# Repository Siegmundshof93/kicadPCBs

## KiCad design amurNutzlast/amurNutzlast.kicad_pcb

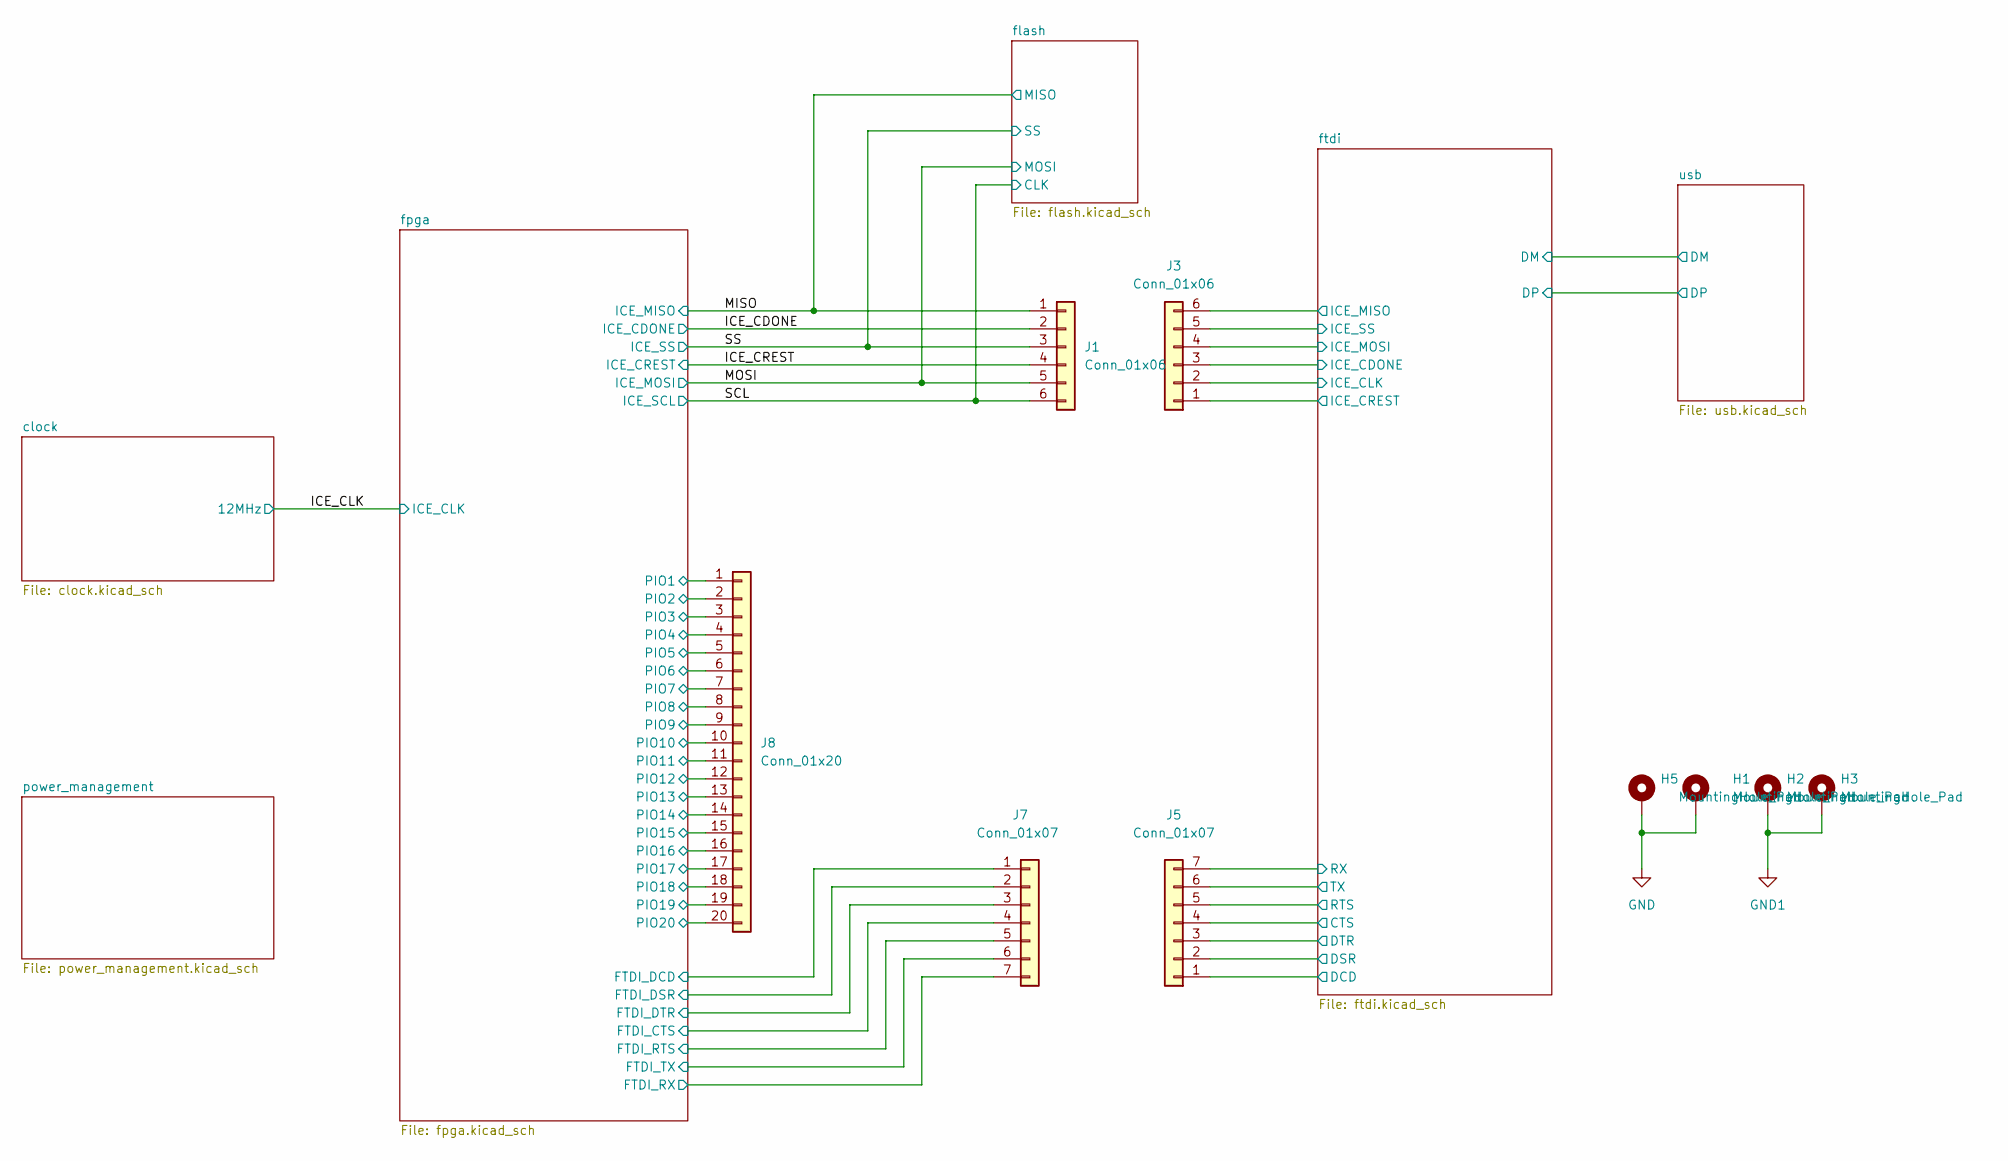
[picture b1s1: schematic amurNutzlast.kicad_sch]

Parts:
H1, H2, H3, H5: MountingHole_Pad; MountingHole_2.5mm_Pad_Via
J1, J3: Conn_01x06; PinHeader_2x03_P2.54mm_Vertical
J5, J7: Conn_01x07; PinHeader_1x07_P2.54mm_Vertical
J8: Conn_01x20; PinHeader_2x10_P2.54mm_Vertical

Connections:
/ICE_CDONE: J1.2; also elsewhere on the board
/ICE_CREST: J1.4; also elsewhere on the board
/MISO: J1.1; also elsewhere on the board
/MOSI: J1.5; also elsewhere on the board
/SCL: J1.6; also elsewhere on the board
/SS: J1.3; also elsewhere on the board
/fpga/FTDI_CTS: J7.4; also elsewhere on the board
/fpga/FTDI_DCD: J7.1; also elsewhere on the board
/fpga/FTDI_DSR: J7.2; also elsewhere on the board
/fpga/FTDI_DTR: J7.3; also elsewhere on the board
/fpga/FTDI_RTS: J7.5; also elsewhere on the board
/fpga/FTDI_RX: J7.7; also elsewhere on the board
/fpga/FTDI_TX: J7.6; also elsewhere on the board
/fpga/PIO1: J8.1; also elsewhere on the board
/fpga/PIO2: J8.2; also elsewhere on the board
/fpga/PIO3: J8.3; also elsewhere on the board
/fpga/PIO4: J8.4; also elsewhere on the board
/fpga/PIO5: J8.5; also elsewhere on the board
/fpga/PIO6: J8.6; also elsewhere on the board
/fpga/PIO7: J8.7; also elsewhere on the board
/fpga/PIO8: J8.8; also elsewhere on the board
/fpga/PIO9: J8.9; also elsewhere on the board
/fpga/PIO10: J8.10; also elsewhere on the board
/fpga/PIO11: J8.11; also elsewhere on the board
/fpga/PIO12: J8.12; also elsewhere on the board
/fpga/PIO13: J8.13; also elsewhere on the board
/fpga/PIO14: J8.14; also elsewhere on the board
/fpga/PIO15: J8.15; also elsewhere on the board
/fpga/PIO16: J8.16; also elsewhere on the board
/fpga/PIO17: J8.17; also elsewhere on the board
/fpga/PIO18: J8.18; also elsewhere on the board
/fpga/PIO19: J8.19; also elsewhere on the board
/fpga/PIO20: J8.20; also elsewhere on the board
/ftdi/CTS: J5.4; also elsewhere on the board
/ftdi/DCD: J5.1; also elsewhere on the board
/ftdi/DSR: J5.2; also elsewhere on the board
/ftdi/DTR: J5.3; also elsewhere on the board
/ftdi/ICE_CDONE: J3.3; also elsewhere on the board
/ftdi/ICE_CLK: J3.2; also elsewhere on the board
/ftdi/ICE_CREST: J3.1; also elsewhere on the board
/ftdi/ICE_MISO: J3.6; also elsewhere on the board
/ftdi/ICE_MOSI: J3.4; also elsewhere on the board
/ftdi/ICE_SS: J3.5; also elsewhere on the board
/ftdi/RTS: J5.5; also elsewhere on the board
/ftdi/RX: J5.7; also elsewhere on the board
/ftdi/TX: J5.6; also elsewhere on the board

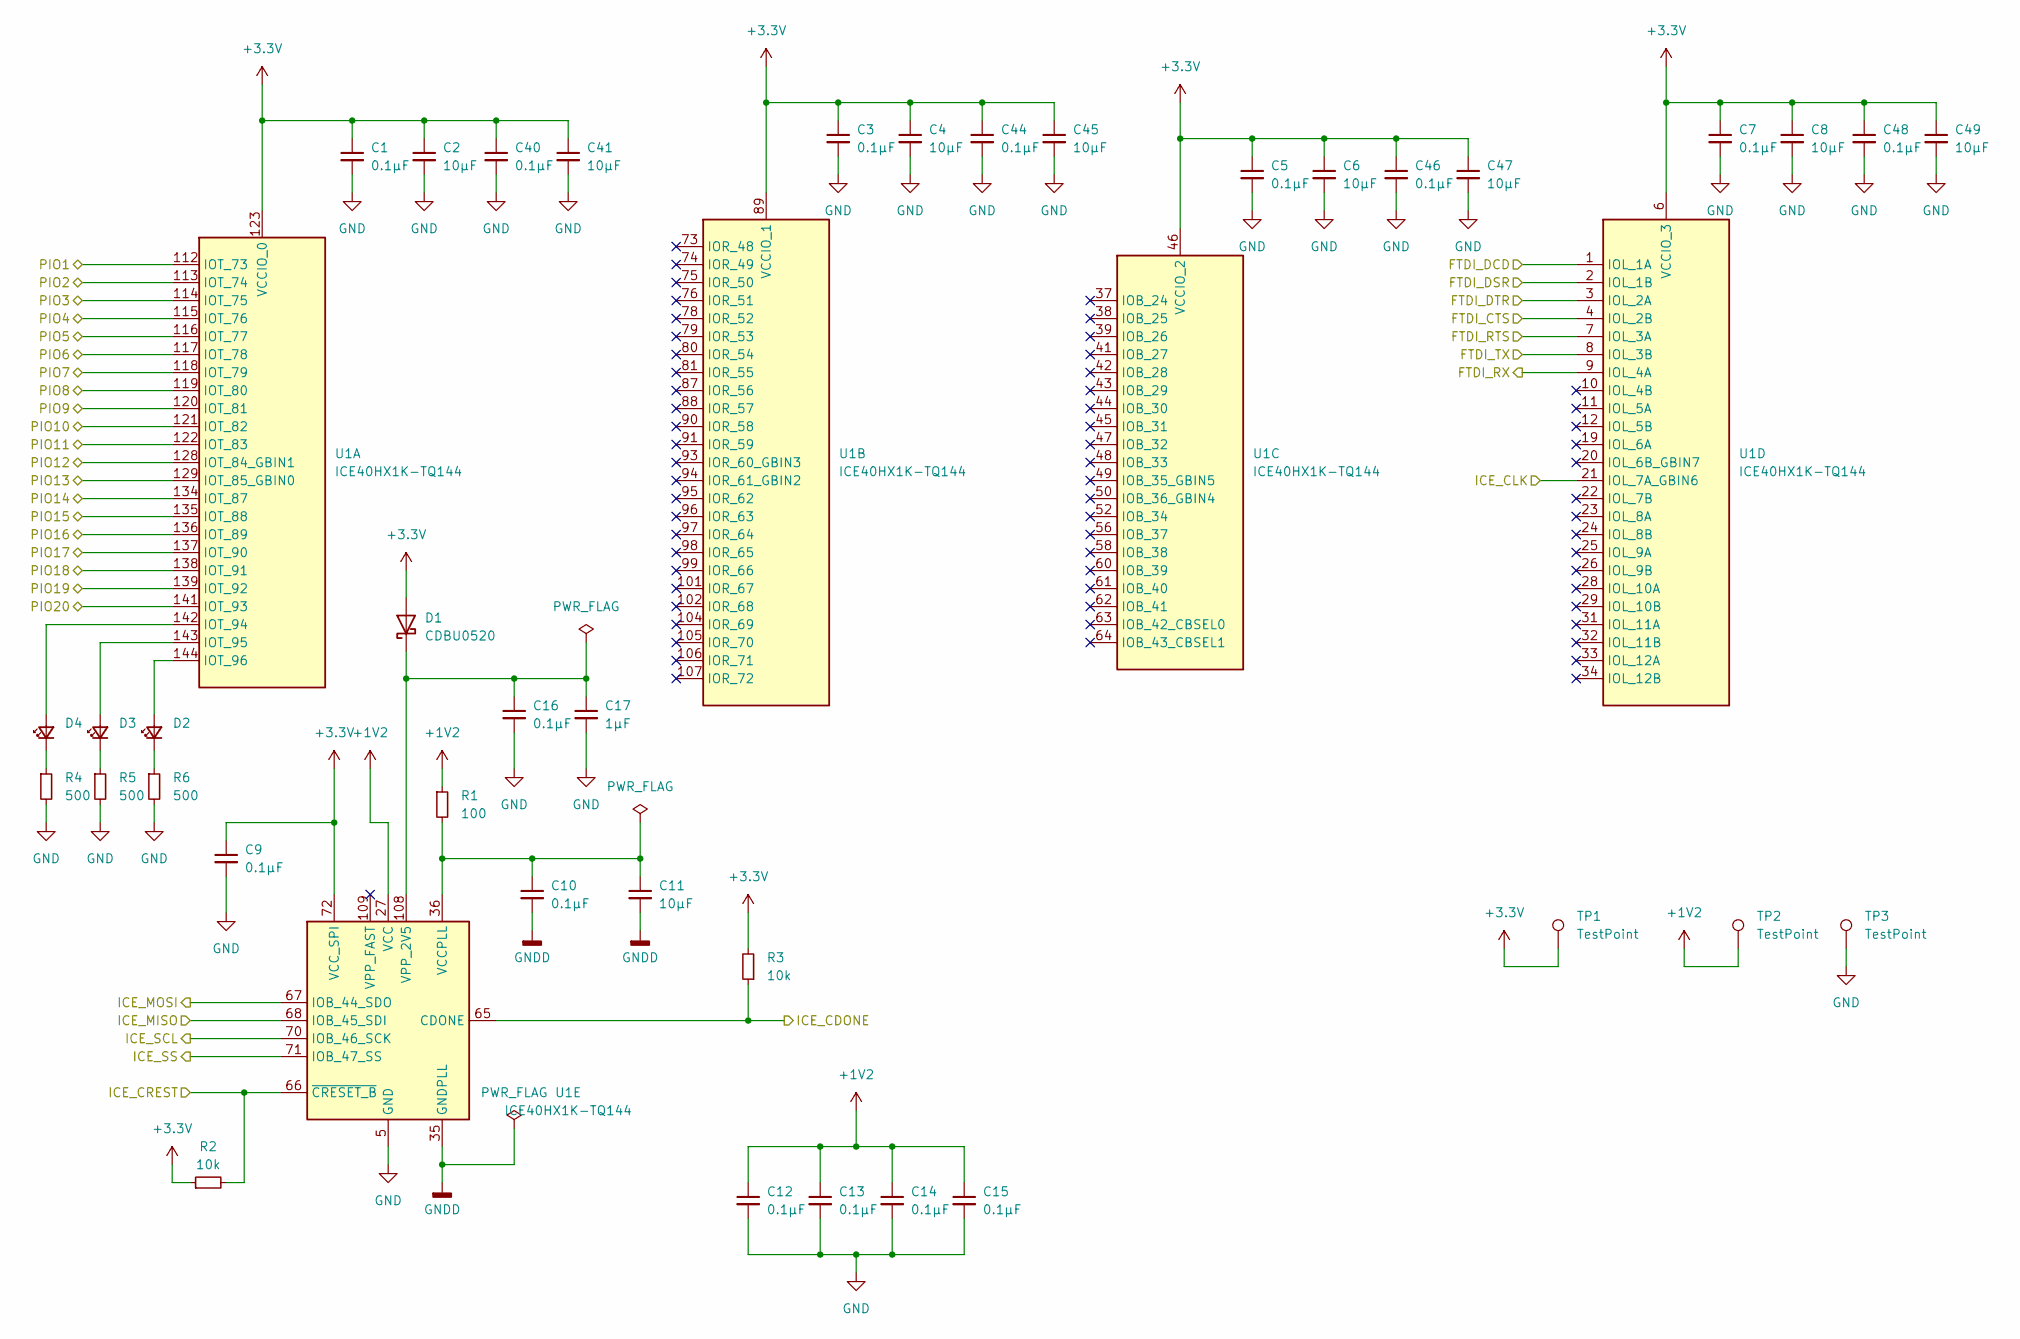
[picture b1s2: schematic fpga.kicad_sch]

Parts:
C1, C3, C5, C7, C9, C10, C12, C13, C14, C15, C16, C40, C44, C46, C48: 0.1µF; C_0603_1608Metric
C2, C4, C6, C8, C11, C41, C45, C47, C49: 10µF; C_0603_1608Metric
C17: 1µF; C_0603_1608Metric
D1: CDBU0520; D_0603_1608Metric
D2, D3, D4: LED_Small; LED_0603_1608Metric
R1: 100; R_0603_1608Metric
R2, R3: 10k; R_0603_1608Metric
R4, R5, R6: 500; R_0603_1608Metric
TP1, TP2, TP3: TestPoint; TestPoint_Pad_D2.5mm
U1: ICE40HX1K-TQ144; TQFP-144_20x20mm_P0.5mm

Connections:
+1V2: C12.1, C13.1, C14.1, C15.1, R1.1, TP2.1, U1.27 (VCC), U1.51 (VCC), U1.92 (VCC), U1.111 (VCC); also elsewhere on the board
/ICE_CDONE: R3.1, U1.65 (CDONE); also elsewhere on the board
/ICE_CLK: U1.21 (IOL_7A_GBIN6); also elsewhere on the board
/ICE_CREST: R2.2, U1.66 (~CRESET_B); also elsewhere on the board
/MISO: U1.68 (IOB_45_SDI); also elsewhere on the board
/MOSI: U1.67 (IOB_44_SDO); also elsewhere on the board
/SCL: U1.70 (IOB_46_SCK); also elsewhere on the board
/SS: U1.71 (IOB_47_SS); also elsewhere on the board
/fpga/FTDI_CTS: U1.4 (IOL_2B); also elsewhere on the board
/fpga/FTDI_DCD: U1.1 (IOL_1A); also elsewhere on the board
/fpga/FTDI_DSR: U1.2 (IOL_1B); also elsewhere on the board
/fpga/FTDI_DTR: U1.3 (IOL_2A); also elsewhere on the board
/fpga/FTDI_RTS: U1.7 (IOL_3A); also elsewhere on the board
/fpga/FTDI_RX: U1.9 (IOL_4A); also elsewhere on the board
/fpga/FTDI_TX: U1.8 (IOL_3B); also elsewhere on the board
/fpga/PIO1: U1.112 (IOT_73); also elsewhere on the board
/fpga/PIO2: U1.113 (IOT_74); also elsewhere on the board
/fpga/PIO3: U1.114 (IOT_75); also elsewhere on the board
/fpga/PIO4: U1.115 (IOT_76); also elsewhere on the board
/fpga/PIO5: U1.116 (IOT_77); also elsewhere on the board
/fpga/PIO6: U1.117 (IOT_78); also elsewhere on the board
/fpga/PIO7: U1.118 (IOT_79); also elsewhere on the board
/fpga/PIO8: U1.119 (IOT_80); also elsewhere on the board
/fpga/PIO9: U1.120 (IOT_81); also elsewhere on the board
/fpga/PIO10: U1.121 (IOT_82); also elsewhere on the board
/fpga/PIO11: U1.122 (IOT_83); also elsewhere on the board
/fpga/PIO12: U1.128 (IOT_84_GBIN1); also elsewhere on the board
/fpga/PIO13: U1.129 (IOT_85_GBIN0); also elsewhere on the board
/fpga/PIO14: U1.134 (IOT_87); also elsewhere on the board
/fpga/PIO15: U1.135 (IOT_88); also elsewhere on the board
/fpga/PIO16: U1.136 (IOT_89); also elsewhere on the board
/fpga/PIO17: U1.137 (IOT_90); also elsewhere on the board
/fpga/PIO18: U1.138 (IOT_91); also elsewhere on the board
/fpga/PIO19: U1.139 (IOT_92); also elsewhere on the board
/fpga/PIO20: U1.141 (IOT_93); also elsewhere on the board
GNDD: C10.2, C11.2, U1.35 (GNDPLL)
unnamed: C16.1, C17.1, D1.1 (K), U1.108 (VPP_2V5)
unnamed: D2.2 (A), U1.144 (IOT_96)
unnamed: D2.1 (K), R6.1
unnamed: D3.2 (A), U1.143 (IOT_95)
unnamed: D3.1 (K), R5.1
unnamed: D4.2 (A), U1.142 (IOT_94)
unnamed: D4.1 (K), R4.1
unnamed: C10.1, C11.1, R1.2, U1.36 (VCCPLL)

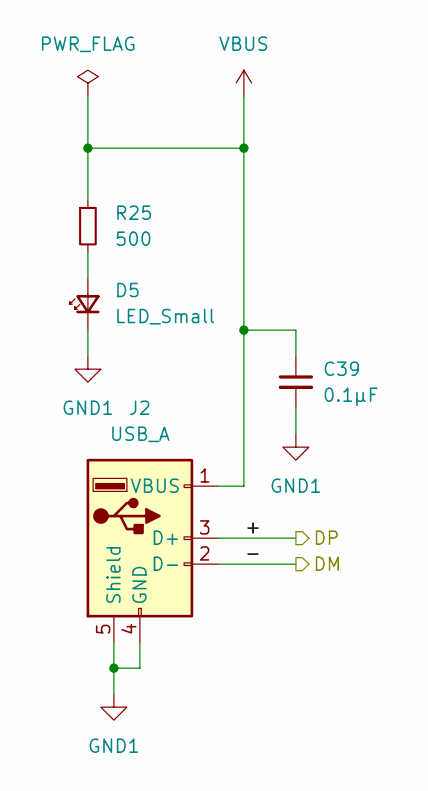
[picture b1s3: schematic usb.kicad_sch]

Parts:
C39: 0.1µF; C_0603_1608Metric
D5: LED_Small; LED_0603_1608Metric
J2: USB_A; USB_A_CNCTech_1001-011-01101_Horizontal
R25: 500; R_0603_1608Metric

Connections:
+5V: J2.2; also elsewhere on the board

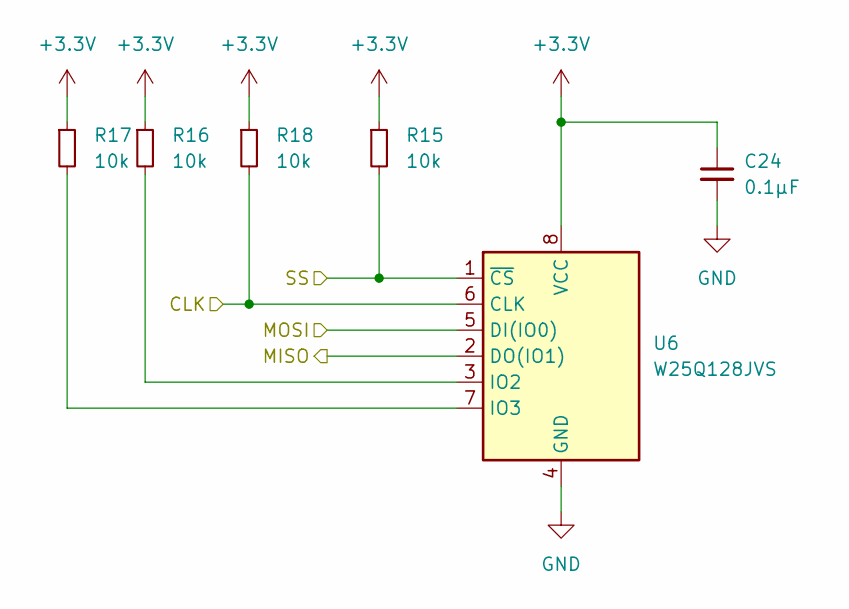
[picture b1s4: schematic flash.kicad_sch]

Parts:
C24: 0.1µF; C_0603_1608Metric
R15, R16, R17, R18: 10k; R_0603_1608Metric
U6: W25Q128JVS; SOIC-8_5.23x5.23mm_P1.27mm

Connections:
/MISO: U6.2 (DO(IO1)); also elsewhere on the board
/MOSI: U6.5 (DI(IO0)); also elsewhere on the board
/SCL: R18.2, U6.6 (CLK); also elsewhere on the board
/SS: R15.2, U6.1 (~CS); also elsewhere on the board
unnamed: R16.2, U6.3 (IO2)
unnamed: R17.2, U6.7 (IO3)

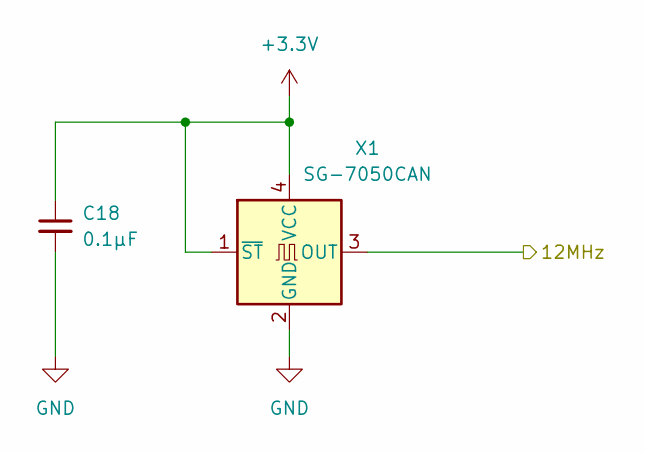
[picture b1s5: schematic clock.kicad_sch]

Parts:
C18: 0.1µF; C_0603_1608Metric
X1: SG-7050CAN; Oscillator_SMD_SeikoEpson_SG8002CA-4Pin_7.0x5.0mm

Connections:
/ICE_CLK: X1.3 (OUT); also elsewhere on the board

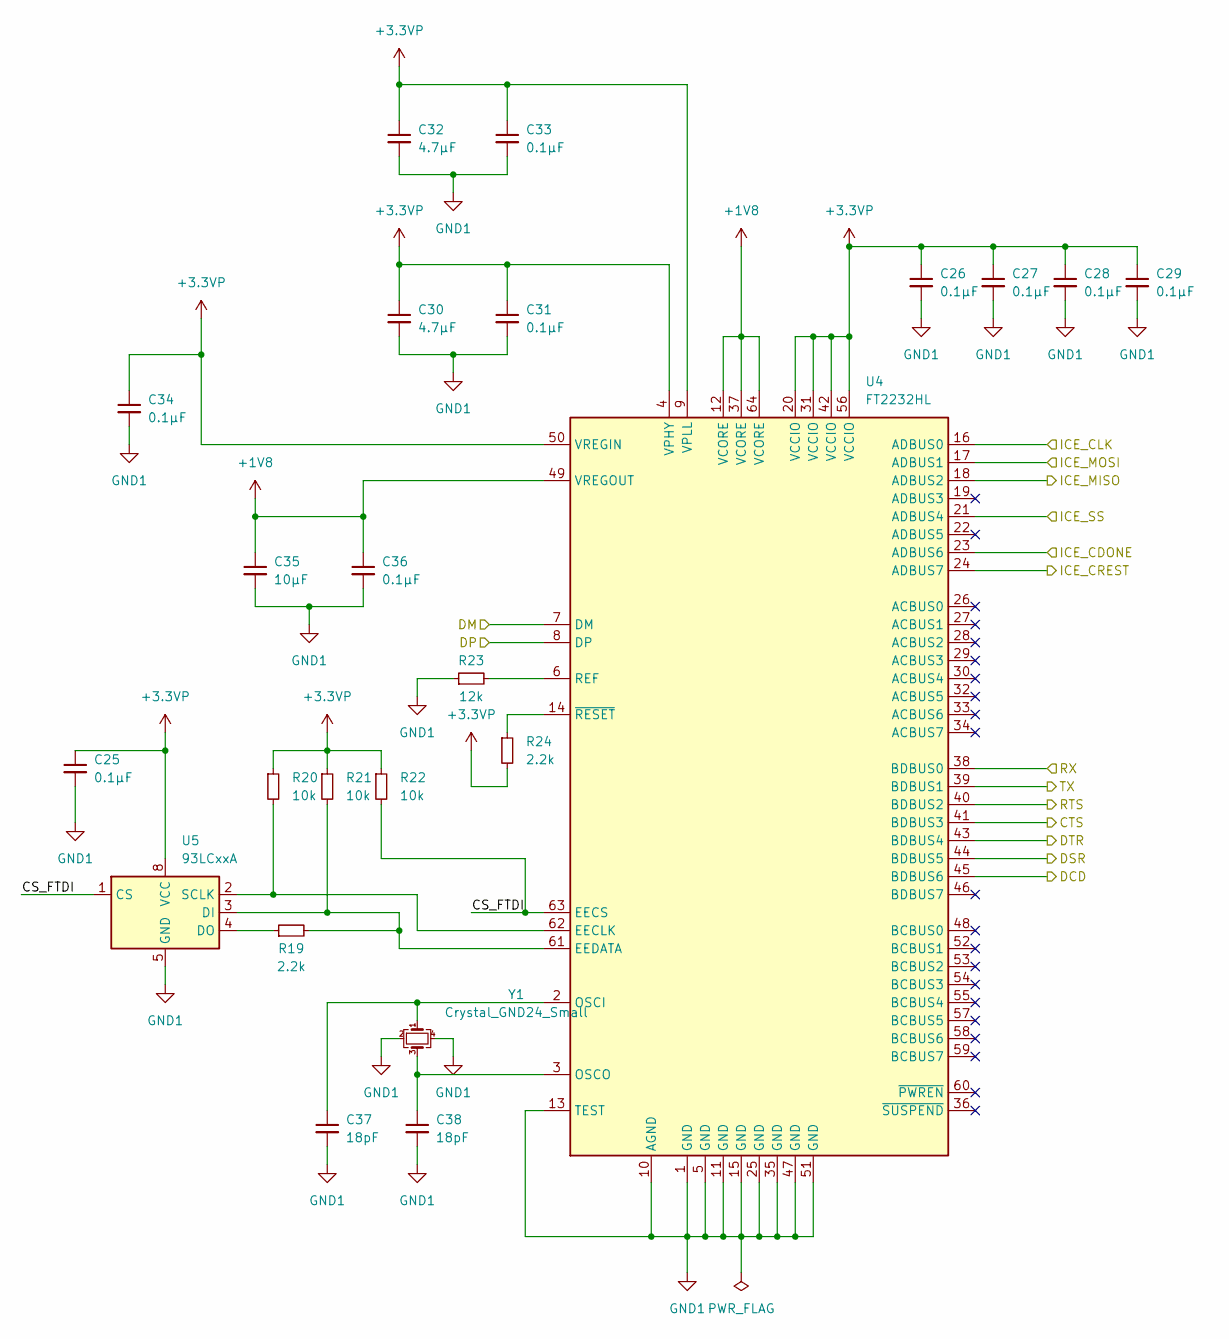
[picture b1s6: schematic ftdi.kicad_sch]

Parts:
C25, C26, C27, C28, C29, C31, C33, C34, C36: 0.1µF; C_0603_1608Metric
C30, C32: 4.7µF; C_0603_1608Metric
C35: 10µF; C_0603_1608Metric
C37, C38: 18pF; C_0603_1608Metric
R19, R24: 2.2k; R_0603_1608Metric
R20, R21, R22: 10k; R_0603_1608Metric
R23: 12k; R_0603_1608Metric
U4: FT2232HL; LQFP-64_10x10mm_P0.5mm
U5: 93LCxxA; SOIC-8_3.9x4.9mm_P1.27mm
Y1: Crystal_GND24_Small; Crystal_SMD_3225-4Pin_3.2x2.5mm

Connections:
+1V8: C35.1, C36.1, U4.12 (VCORE), U4.37 (VCORE), U4.49 (VREGOUT), U4.64 (VCORE)
/ftdi/CS_FTDI: R22.2, U4.63 (EECS), U5.1 (CS)
/ftdi/CTS: U4.41 (BDBUS3); also elsewhere on the board
/ftdi/DCD: U4.45 (BDBUS6); also elsewhere on the board
/ftdi/DSR: U4.44 (BDBUS5); also elsewhere on the board
/ftdi/DTR: U4.43 (BDBUS4); also elsewhere on the board
/ftdi/ICE_CDONE: U4.23 (ADBUS6); also elsewhere on the board
/ftdi/ICE_CLK: U4.16 (ADBUS0); also elsewhere on the board
/ftdi/ICE_CREST: U4.24 (ADBUS7); also elsewhere on the board
/ftdi/ICE_MISO: U4.18 (ADBUS2); also elsewhere on the board
/ftdi/ICE_MOSI: U4.17 (ADBUS1); also elsewhere on the board
/ftdi/ICE_SS: U4.21 (ADBUS4); also elsewhere on the board
/ftdi/RTS: U4.40 (BDBUS2); also elsewhere on the board
/ftdi/RX: U4.38 (BDBUS0); also elsewhere on the board
/ftdi/TX: U4.39 (BDBUS1); also elsewhere on the board
/usb/+: U4.8 (DP); also elsewhere on the board
/usb/-: U4.7 (DM); also elsewhere on the board
unnamed: R20.2, U4.62 (EECLK), U5.2 (SCLK)
unnamed: R19.2, R21.2, U4.61 (EEDATA), U5.3 (DI)
unnamed: C37.1, U4.2 (OSCI), Y1.1
unnamed: C38.1, U4.3 (OSCO), Y1.3
unnamed: R23.2, U4.6 (REF)
unnamed: R24.1, U4.14 (~RESET)
unnamed: R19.1, U5.4 (DO)

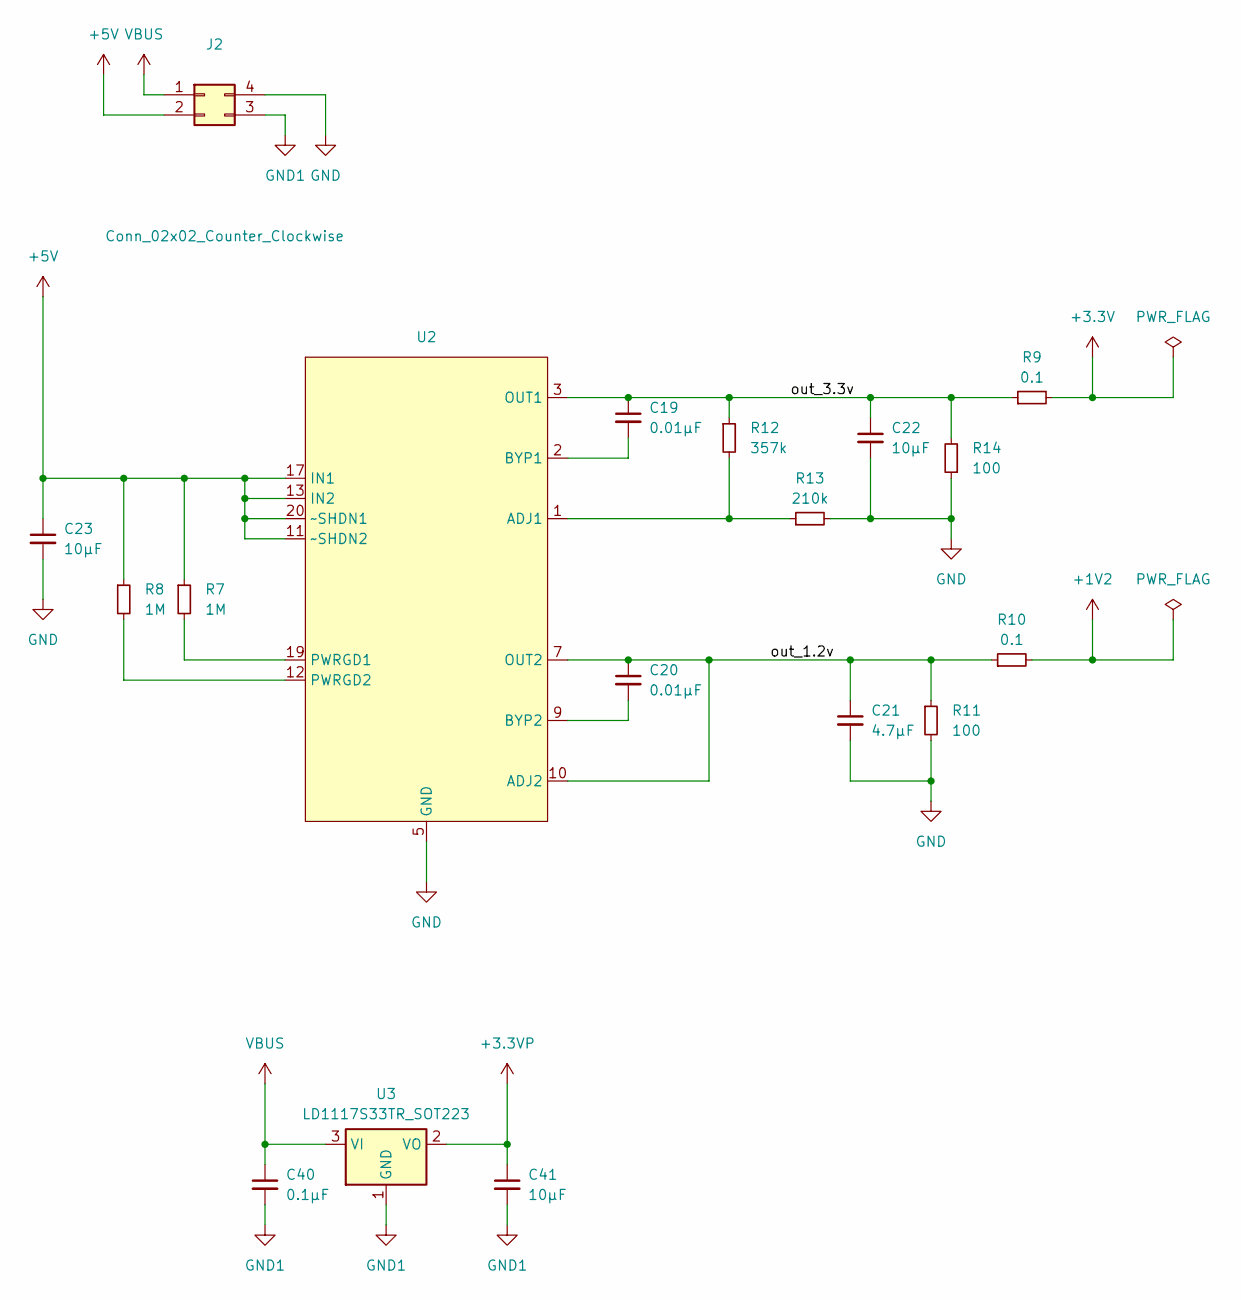
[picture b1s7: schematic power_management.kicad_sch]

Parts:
C19, C20: 0.01µF; C_0603_1608Metric
C21: 4.7µF; C_0603_1608Metric
C22, C23, C41: 10µF; C_0603_1608Metric
C40: 0.1µF; C_0603_1608Metric
J2: Conn_02x02_Counter_Clockwise; PinHeader_2x02_P2.54mm_Vertical
R7, R8: 1M; R_0603_1608Metric
R9, R10: 0.1; R_0603_1608Metric
R11, R14: 100; R_0603_1608Metric
R12: 357k; R_0603_1608Metric
R13: 210k; R_0603_1608Metric
U2: HTSSOP-20-1EP_4.4x6.5mm_P0.65mm_EP2.74x3.86mm
U3: LD1117S33TR_SOT223; SOT-223-3_TabPin2

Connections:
+1V2: R10.2; also elsewhere on the board
+5V: C23.1, J2.2, R7.1, R8.1, U2.11 (~SHDN2), U2.13 (IN2), U2.14 (IN2), U2.17 (IN1), U2.18 (IN1), U2.20 (~SHDN1)
/power_management/out_1.2v: C20.1, C21.1, R10.1, R11.1, U2.7 (OUT2), U2.8 (OUT2), U2.10 (ADJ2)
/power_management/out_3.3v: C19.1, C22.1, R9.1, R12.1, R14.2, U2.3 (OUT1), U2.4 (OUT1)
unnamed: R12.2, R13.1, U2.1 (ADJ1)
unnamed: C19.2, U2.2 (BYP1)
unnamed: C20.2, U2.9 (BYP2)
unnamed: R7.2, U2.19 (PWRGD1)
unnamed: R8.2, U2.12 (PWRGD2)

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
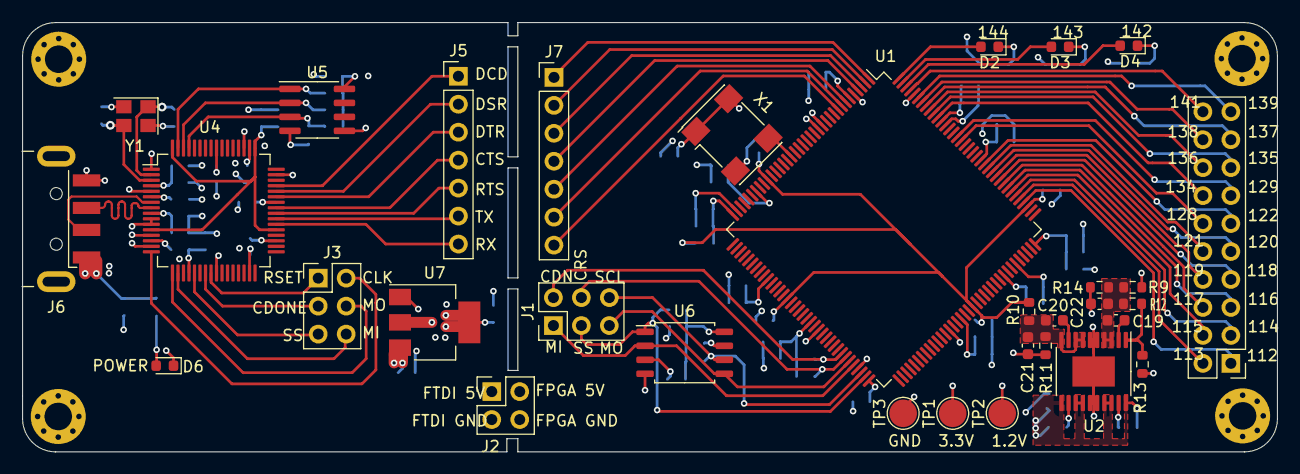
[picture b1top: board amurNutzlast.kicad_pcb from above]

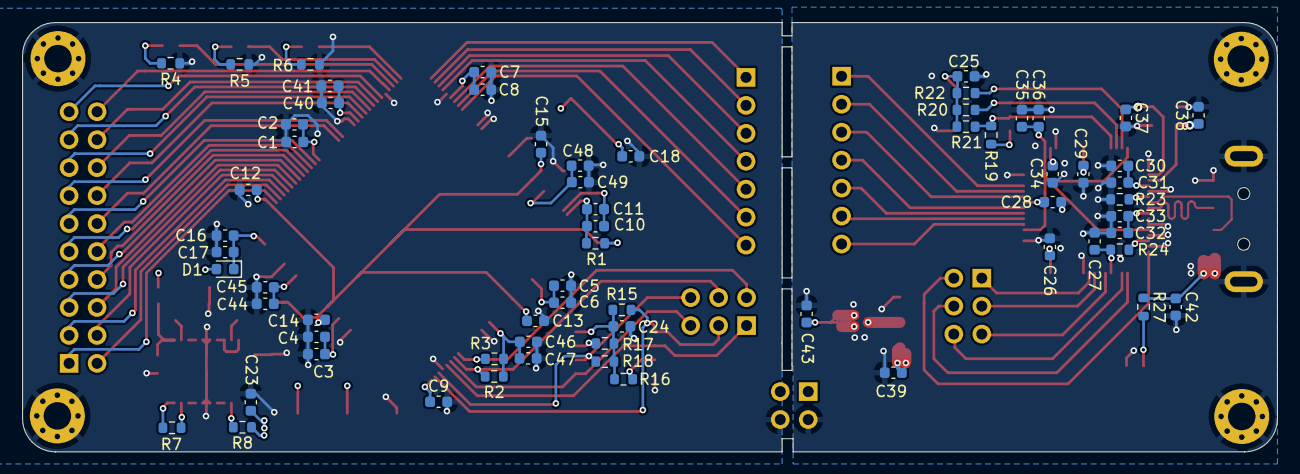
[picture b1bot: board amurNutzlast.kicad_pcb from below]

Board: 4 copper layers, 114.0 x 39.0 mm, 101 parts (65 on the bottom side), 84 nets.

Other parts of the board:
C42: 0.1µF; C_0603_1608Metric
C43: 10µF; C_0603_1608Metric
D6: LED_Small; LED_0603_1608Metric
J6: USB_A; USB_A_CNCTech_1001-011-01101_Horizontal
R27: 500; R_0603_1608Metric
U7: LD1117S33TR_SOT223; SOT-223-3_TabPin2

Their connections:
/usb/+: J6.3 (D+); also elsewhere on the board
/usb/-: J6.2 (D-); also elsewhere on the board
unnamed: D6.2 (A), R27.2

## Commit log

2023-10-15 Fpga chip only
2023-10-15 working on the FTDI design in kicad FPGA prototype board
2023-10-16 ftdi schematic was added apart of the USB
2023-10-17 finisched design schematics + pdf
2023-10-19 layout start
2023-10-20 deleted 3.3 converter for ftdi and moved USB to a hierarhical sheet
2023-10-22 layout ftdi placement
2023-10-22 ftdi layout continuation
2023-10-24 ftdi layout finish
2023-10-25 started FPGA
2023-10-26 placement finished
2023-10-29 gpio connected
2023-10-29 finished pcb
